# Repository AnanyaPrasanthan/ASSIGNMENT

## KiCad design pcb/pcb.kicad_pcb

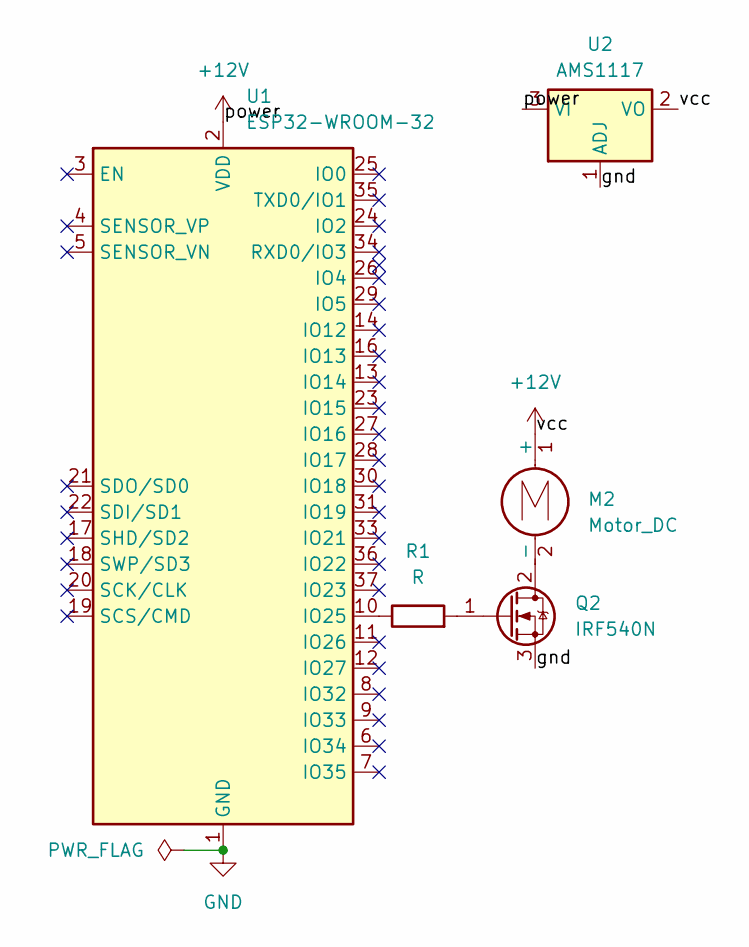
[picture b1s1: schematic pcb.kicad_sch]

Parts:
M2: Motor_DC; TerminalBlock_RND_205-00232_1x02_P5.08mm_Horizontal
Q2: IRF540N; TO-220-3_Vertical
R1: R; R_0201_0603Metric
U1: ESP32-WROOM-32
U2: AMS1117; SOT-223-3_TabPin2

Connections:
+12V: M2.1 (+), U1.2 (VDD), U2.2 (VO), U2.3 (VI)
/gnd: Q2.3 (S), U2.1 (ADJ)
GND: U1.1 (GND), U1.15 (GND), U1.38 (GND), U1.39 (GND)
unnamed: M2.2 (-), Q2.2 (D)
unnamed: Q2.1 (G), R1.2
unnamed: R1.1, U1.10 (IO25)

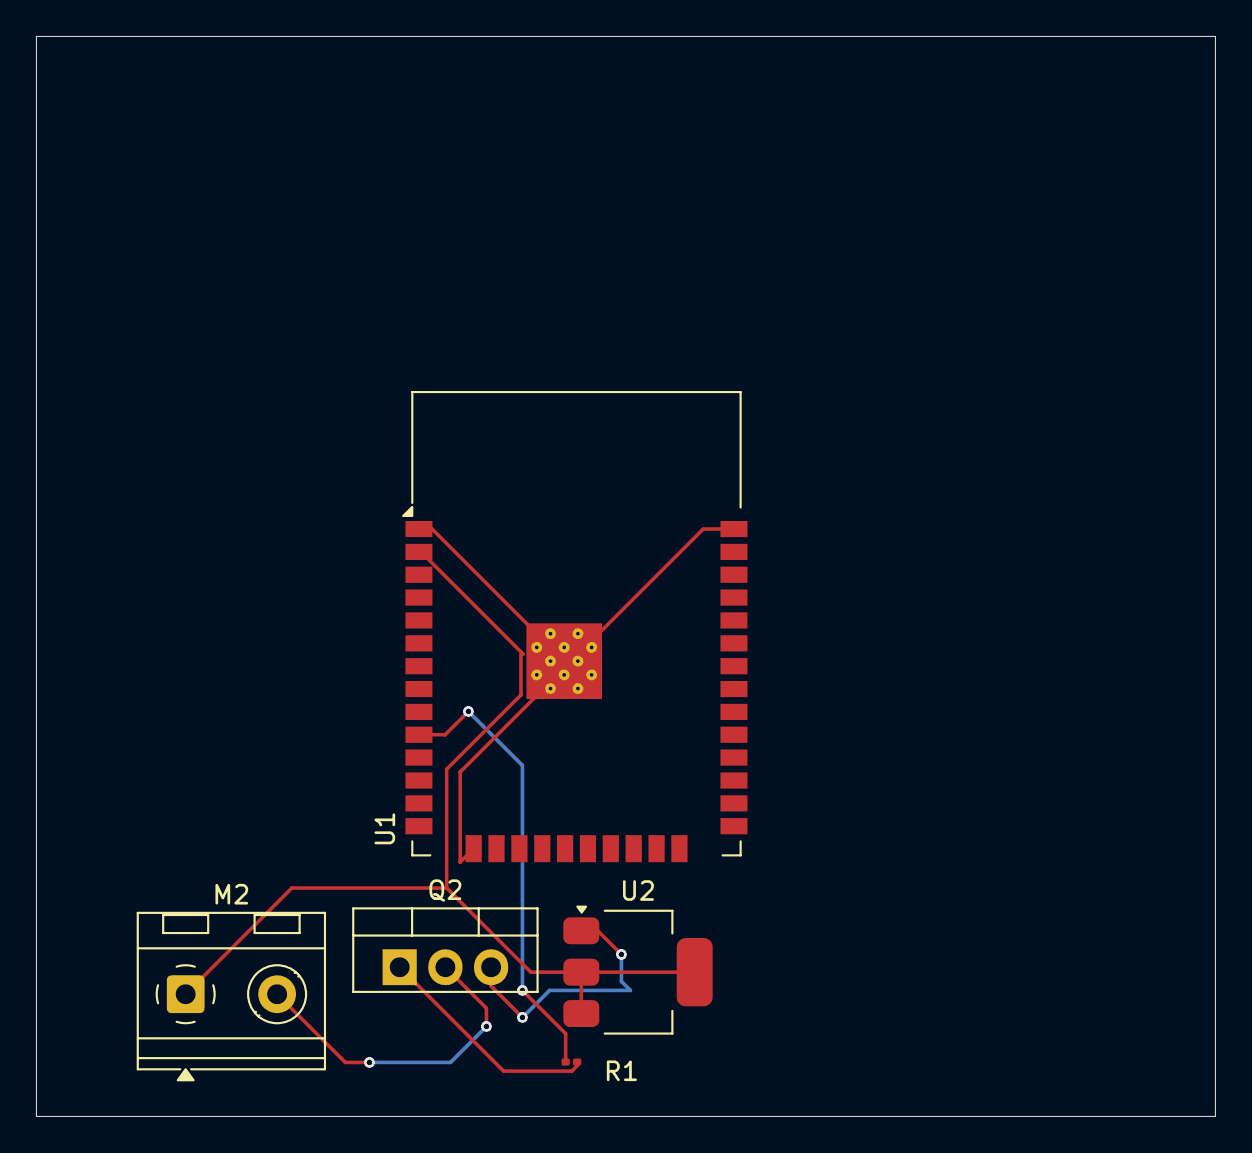
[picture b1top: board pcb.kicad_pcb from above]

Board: 2 copper layers, 65.5 x 60.0 mm, 5 parts (0 on the bottom side), 6 nets.
